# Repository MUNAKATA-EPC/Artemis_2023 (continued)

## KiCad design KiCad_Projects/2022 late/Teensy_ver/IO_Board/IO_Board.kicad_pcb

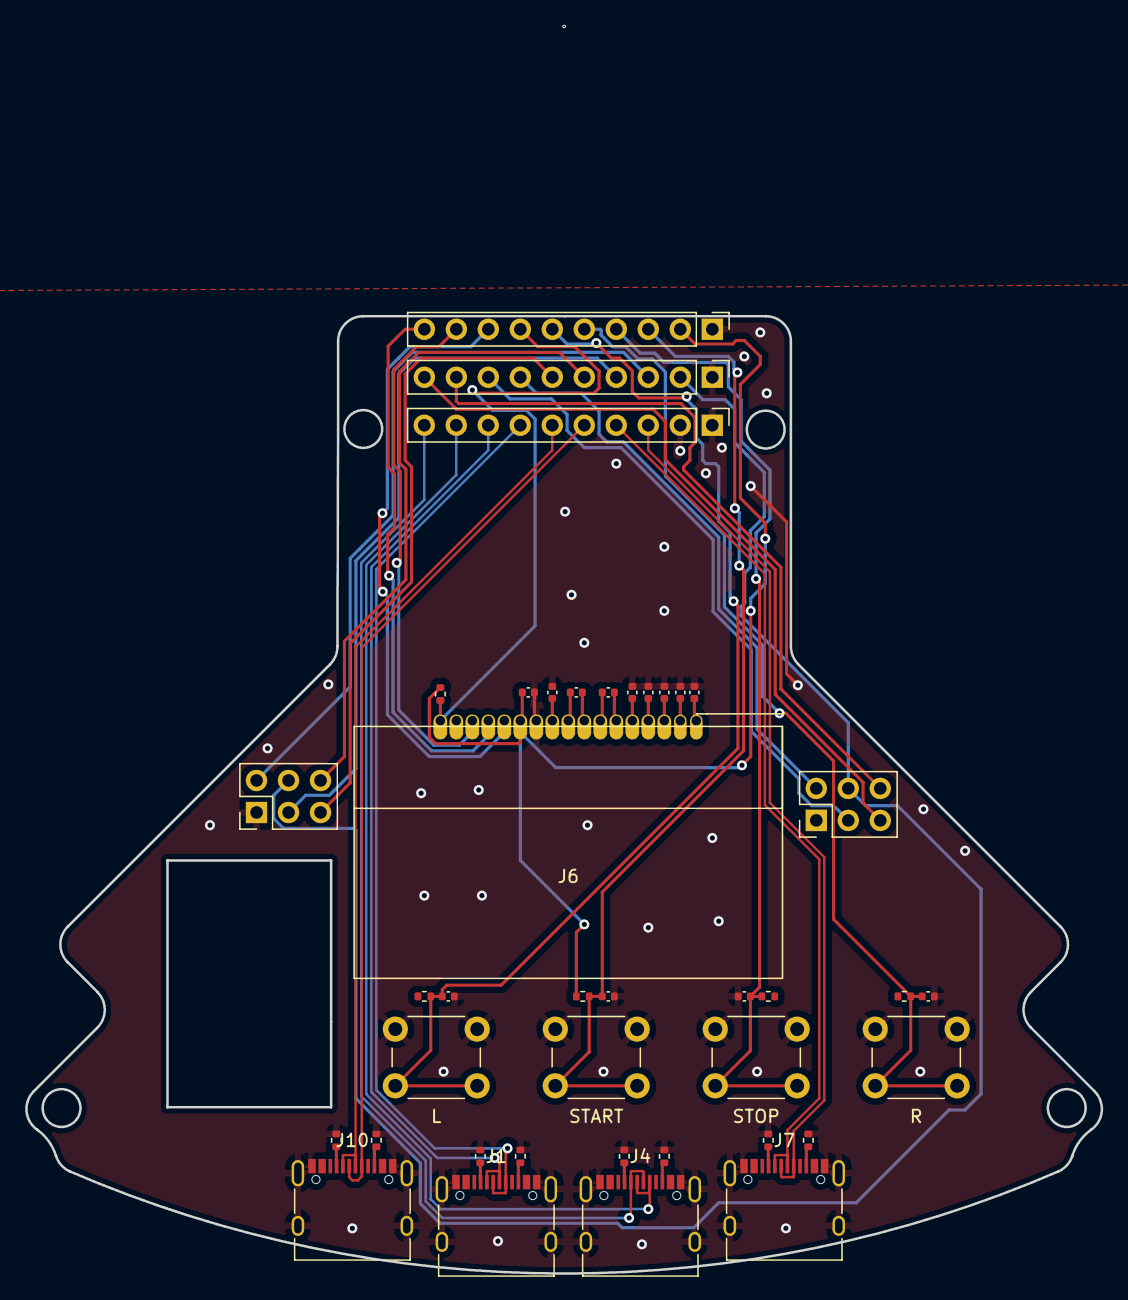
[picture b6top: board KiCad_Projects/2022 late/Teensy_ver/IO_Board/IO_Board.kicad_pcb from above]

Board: 2 copper layers, 85.4 x 76.0 mm, 40 parts (0 on the bottom side), 45 nets.

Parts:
C1, C2, C9, C13: C; C_0402_1005Metric
C3, C4, C5, C6, C7, C8, C10, C11, C12: C_Small; C_0402_1005Metric
J1, J4, J7, J10: USB_C_Receptacle_USB2.0; USB_C_Receptacle_XKB_U262-16XN-4BVC11
J2, J9: Conn_01x06_Female; PinHeader_2x03_P2.54mm_Vertical
J3, J5, J8: Conn_01x10_Female; PinHeader_1x10_P2.54mm_Vertical
J6: Conn_01x17_Female; LCDmodule_aqm1248a
L: SW_DIP_x01; SW_PUSH_6mm_H5mm
R: SW_DIP_x01; SW_PUSH_6mm_H5mm
R1, R4, R5, R8, R9: 10K; R_0402_1005Metric
R2, R3, R6, R7, R10, R11, R12, R13: R; R_0402_1005Metric
START: SW_DIP_x01; SW_PUSH_6mm_H5mm
STOP: SW_DIP_x01; SW_PUSH_6mm_H5mm

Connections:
+3V3: C4.2, J5.2, J6.6, R1.1, R4.2, R5.1, R8.1, R9.1
+5V: J2.4, J8.2, J9.4
CS: J5.7, J6.1, R4.1
Cam D+: J3.9, J4.A6 (D+), J4.B6 (D+)
Cam D-: J3.10, J4.A7 (D-), J4.B7 (D-)
GND: C1.2, C2.2, C3.1, C4.1, C7.1, C8.1, C9.2, C10.1, C11.1, C12.1, C13.2, J1.A1 (GND), J1.A12 (GND), J1.B1 (GND), J1.B12 (GND), J1.S1 (SHIELD), J2.1, J3.1, J3.2, J4.A1 (GND), J4.A12 (GND), J4.B1 (GND), J4.B12 (GND), J4.S1 (SHIELD), J5.1, J6.7, J7.A1 (GND), J7.A12 (GND), J7.B1 (GND), J7.B12 (GND), J7.S1 (SHIELD), J8.1, J9.1, J10.A1 (GND), J10.A12 (GND), J10.B1 (GND), J10.B12 (GND), J10.S1 (SHIELD), L.1, R.1, R2.2, R3.2, R6.2, R7.2, R10.2, R11.2, R12.2, R13.2, START.1, STOP.1
Gyro D+: J3.3, J7.A6 (D+), J7.B6 (D+)
Gyro D-: J3.4, J7.A7 (D-), J7.B7 (D-)
L: C13.1, J5.6, L.2, R9.2
Line D+: J3.5, J10.A6 (D+), J10.B6 (D+)
Line D-: J3.6, J10.A7 (D-), J10.B7 (D-)
MISO 1: J2.3, J8.4
MISO 2: J8.8, J9.3
MOSI: J5.8, J6.5
MOSI 1: J2.6, J8.5
MOSI 2: J8.9, J9.6
unnamed: C3.2, J6.8
unnamed: C5.1, J6.9
unnamed: C5.2, J6.10
unnamed: C6.1, J6.11
unnamed: C6.2, J6.12
unnamed: C7.2, J6.13
unnamed: C8.2, J6.14
unnamed: C10.2, J6.15
unnamed: C11.2, J6.16
unnamed: C12.2, J6.17
unnamed: J1.A5 (CC1), R2.1
unnamed: J1.B5 (CC2), R3.1
unnamed: J4.A5 (CC1), R6.1
unnamed: J4.B5 (CC2), R7.1
unnamed: J7.A5 (CC1), R10.1
unnamed: J7.B5 (CC2), R11.1
unnamed: J10.A5 (CC1), R12.1
unnamed: J10.B5 (CC2), R13.1
R: C9.1, J5.5, R.2, R8.2
RS: J5.9, J6.3
Reset 1: J2.2, J8.3
Reset 2: J8.7, J9.2
SCK: J5.10, J6.4
SCK 1: J2.5, J8.6
SCK 2: J8.10, J9.5
Teensy D+: J1.A6 (D+), J1.B6 (D+), J3.7
Teensy D-: J1.A7 (D-), J1.B7 (D-), J3.8
start: C1.1, J5.3, R1.2, START.2
stop: C2.1, J5.4, R5.2, STOP.2
